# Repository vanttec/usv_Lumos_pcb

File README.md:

# vanttec-usv_Lumos_pcb 
PCB Led Strip/Expansión

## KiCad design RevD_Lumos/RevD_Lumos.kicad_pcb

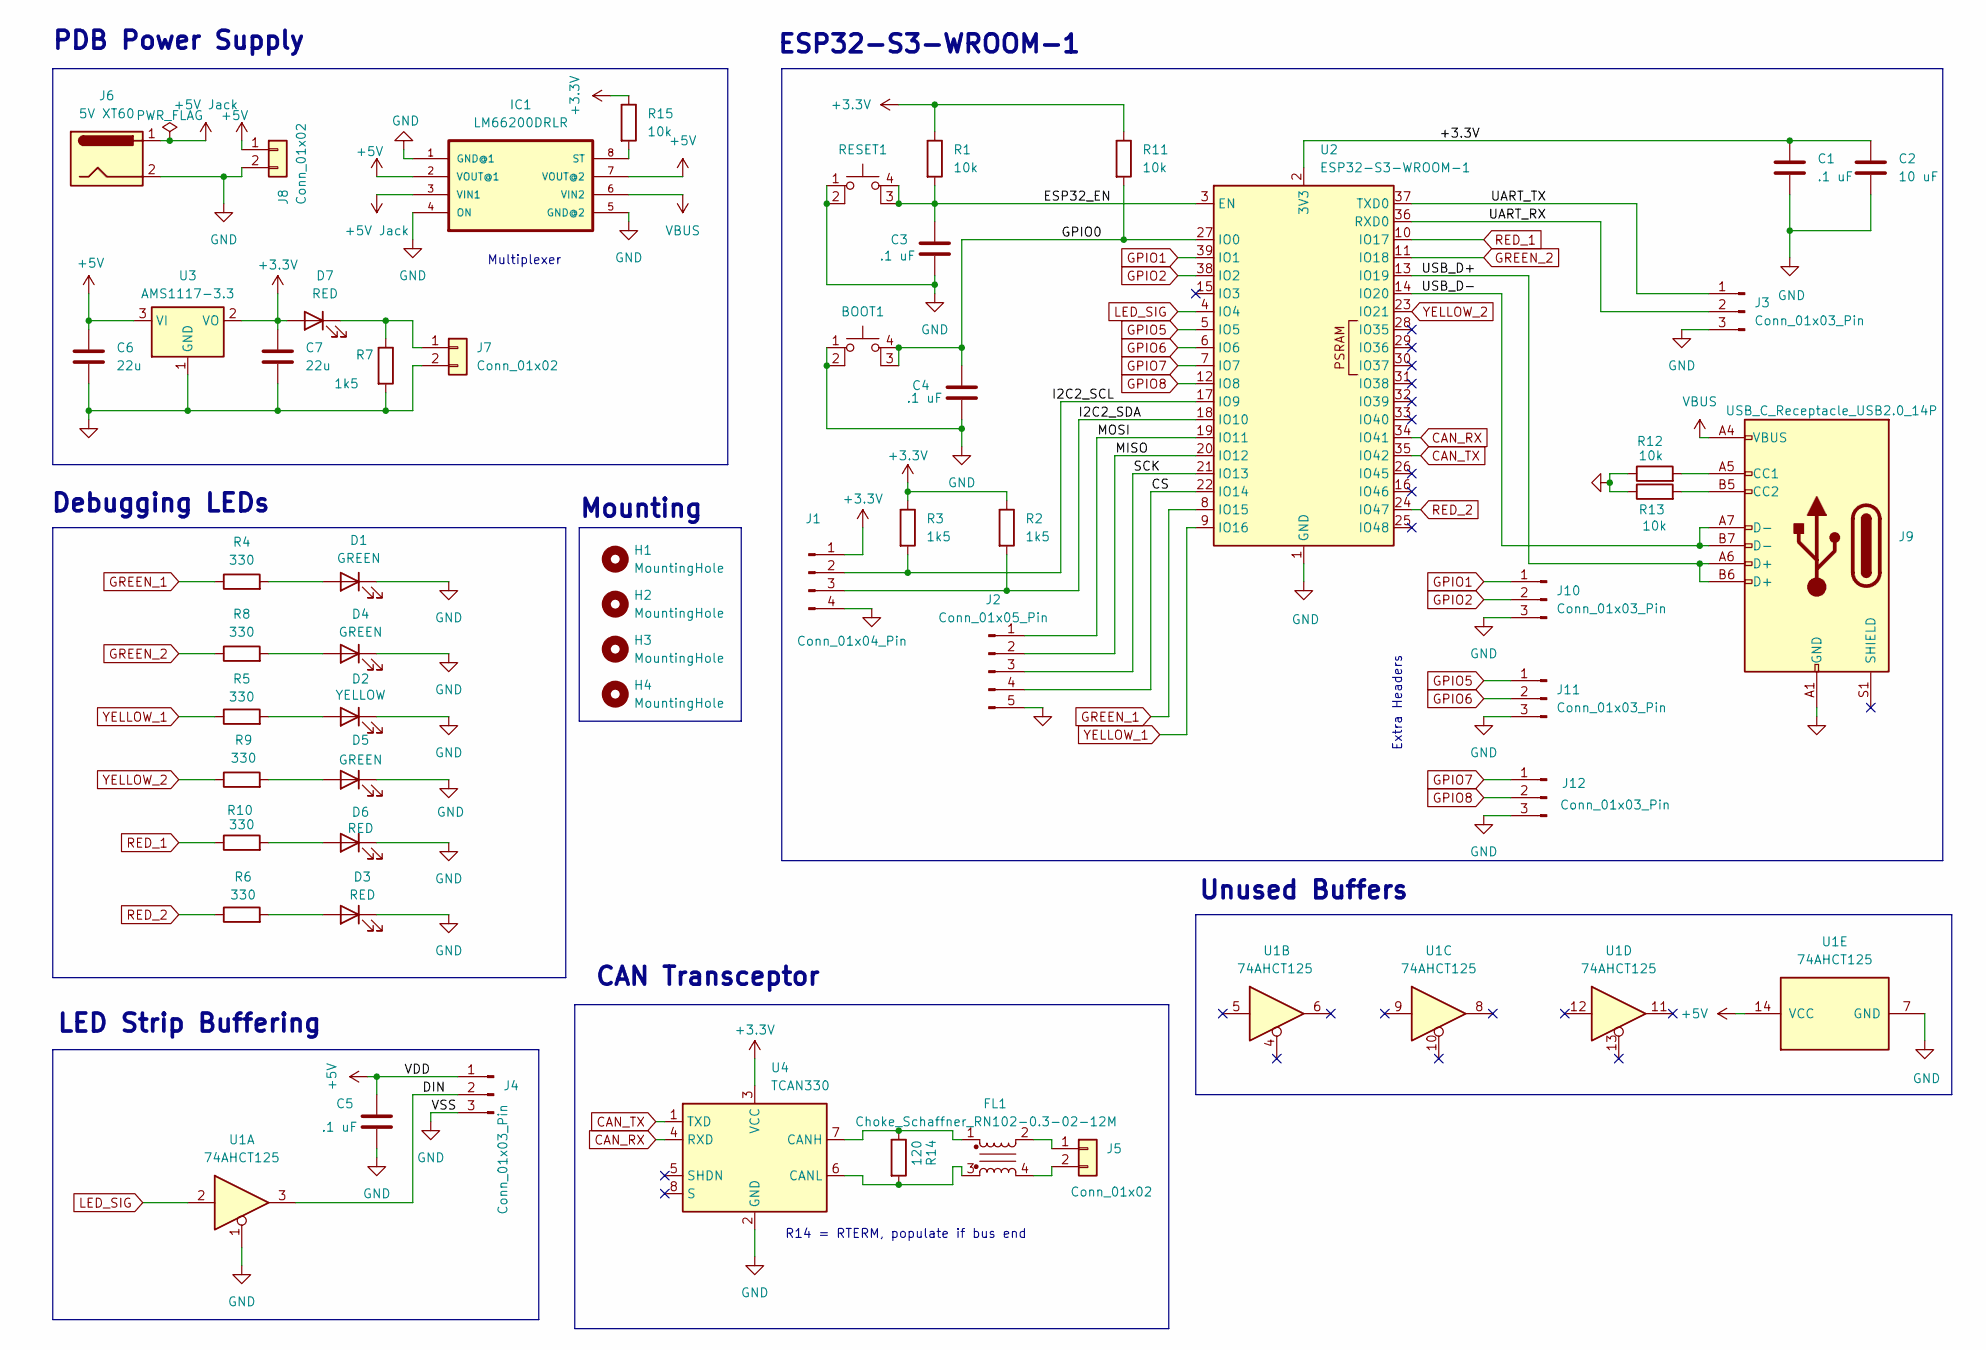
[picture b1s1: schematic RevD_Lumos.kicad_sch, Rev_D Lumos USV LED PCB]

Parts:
BOOT1: SW_MEC_5E; SW_MEC_5GSH9
C1, C3, C4, C5: .1 uF; C_0402_1005Metric
C2: 10 uF; C_0402_1005Metric
C6, C7: 22u; C_0805_2012Metric
D1, D4, D5: GREEN; LED_0603_1608Metric
D2: YELLOW; LED_0603_1608Metric
D3, D6, D7: RED; LED_0603_1608Metric
FL1: Choke_Schaffner_RN102-0.3-02-12M; Choke_Schaffner_RN102-04-14.0x14.0mm
H1, H2, H3, H4: MountingHole; MountingHole_2.2mm_M2
IC1: LM66200DRLR; SOT-5X3_DRL_TEX
J1: Conn_01x04_Pin; PinHeader_1x04_P2.54mm_Vertical
J2: Conn_01x05_Pin; PinHeader_1x05_P2.54mm_Vertical
J3, J4, J10, J11, J12: Conn_01x03_Pin; PinHeader_1x03_P2.54mm_Vertical
J5, J7, J8: Conn_01x02; PinHeader_1x02_P2.54mm_Vertical
J6: 5V XT60; BarrelJack_Wuerth_694102107102_1.0x3.9mm
J9: USB_C_Receptacle_USB2.0_14P; USB_C_Receptacle_Molex_105450-0101
R1, R11, R12, R13, R15: 10k; R_0402_1005Metric
R2, R3, R7: 1k5; R_0402_1005Metric
R4, R5, R6, R8, R9, R10: 330; R_0402_1005Metric
R14: 120; R_0402_1005Metric
RESET1: SW_MEC_5E; SW_MEC_5GSH9
U1: 74AHCT125; SOIC-14_3.9x8.7mm_P1.27mm
U2: ESP32-S3-WROOM-1
U3: AMS1117-3.3; SOT-223-3_TabPin2
U4: TCAN330; SOIC-8-1EP_3.9x4.9mm_P1.27mm_EP2.29x3mm

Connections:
+3.3V: C1.1, C2.1, C7.1, D7.2 (A), J1.1, R1.1, R2.1, R3.1, R11.1, R15.1, U2.2 (3V3), U3.2 (VO), U4.3 (VCC)
+5V: C5.1, C6.1, IC1.2 (VOUT@1), IC1.7 (VOUT@2), J4.1, J8.1, U1.14 (VCC), U3.3 (VI)
+5V Jack: IC1.3 (VIN1), J6.1
/CS: J2.4, U2.22 (IO14)
/DIN: J4.2, U1.3
/ESP32_EN: C3.1, R1.2, RESET1.3 (K), RESET1.4 (A), U2.3 (EN)
/GPIO0: BOOT1.3 (K), BOOT1.4 (A), C4.1, R11.2, U2.27 (IO0)
/I2C2_SCL: J1.2, R3.2, U2.17 (IO9)
/I2C2_SDA: J1.3, R2.2, U2.18 (IO10)
/MISO: J2.2, U2.20 (IO12)
/MOSI: J2.1, U2.19 (IO11)
/SCK: J2.3, U2.21 (IO13)
/UART_RX: J3.2, U2.36 (RXD0)
/UART_TX: J3.1, U2.37 (TXD0)
/USB_D+: J9.A6 (D+), J9.B6 (D+), U2.13 (IO19)
/USB_D-: J9.A7 (D-), J9.B7 (D-), U2.14 (IO20)
CAN_RX: U2.34 (IO41), U4.4 (RXD)
CAN_TX: U2.35 (IO42), U4.1 (TXD)
GND: BOOT1.1, BOOT1.2, C1.2, C2.2, C3.2, C4.2, C5.2, C6.2, C7.2, D1.1 (K), D2.1 (K), D3.1 (K), D4.1 (K), D5.1 (K), D6.1 (K), IC1.1 (GND@1), IC1.4 (ON), IC1.5 (GND@2), J1.4, J2.5, J3.3, J4.3, J6.2, J7.2, J8.2, J9.A1 (GND), J9.A12 (GND), J9.B1 (GND), J9.B12 (GND), J10.3, J11.3, J12.3, R7.2, R12.1, R13.1, RESET1.1, RESET1.2, U1.1, U1.7 (GND), U2.1 (GND), U2.40 (GND), U2.41 (GND), U3.1 (GND), U4.2 (GND)
GPIO1: J10.1, U2.39 (IO1)
GPIO2: J10.2, U2.38 (IO2)
GPIO5: J11.1, U2.5 (IO5)
GPIO6: J11.2, U2.6 (IO6)
GPIO7: J12.1, U2.7 (IO7)
GPIO8: J12.2, U2.12 (IO8)
GREEN_1: R4.1, U2.8 (IO15)
GREEN_2: R8.1, U2.11 (IO18)
LED_SIG: U1.2, U2.4 (IO4)
unnamed: D1.2 (A), R4.2
unnamed: D2.2 (A), R5.2
unnamed: D3.2 (A), R6.2
unnamed: D4.2 (A), R8.2
unnamed: D5.2 (A), R9.2
unnamed: D6.2 (A), R10.2
unnamed: D7.1 (K), J7.1, R7.1
unnamed: IC1.8 (ST), R15.2
unnamed: FL1.2, J5.1
unnamed: FL1.4, J5.2
unnamed: J9.A5 (CC1), R12.2
unnamed: J9.B5 (CC2), R13.2
unnamed: FL1.1, R14.1, U4.7 (CANH)
unnamed: FL1.3, R14.2, U4.6 (CANL)
RED_1: R10.1, U2.10 (IO17)
RED_2: R6.1, U2.24 (IO47)
VBUS: IC1.6 (VIN2), J9.A4 (VBUS), J9.A9 (VBUS), J9.B4 (VBUS), J9.B9 (VBUS)
YELLOW_1: R5.1, U2.9 (IO16)
YELLOW_2: R9.1, U2.23 (IO21)

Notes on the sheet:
Unused Buffers
Debugging LEDs
CAN Transceptor
Extra Headers
R14 = RTERM, populate if bus end
LED Strip Buffering
Multiplexer
Mounting
PDB Power Supply
ESP32-S3-WROOM-1

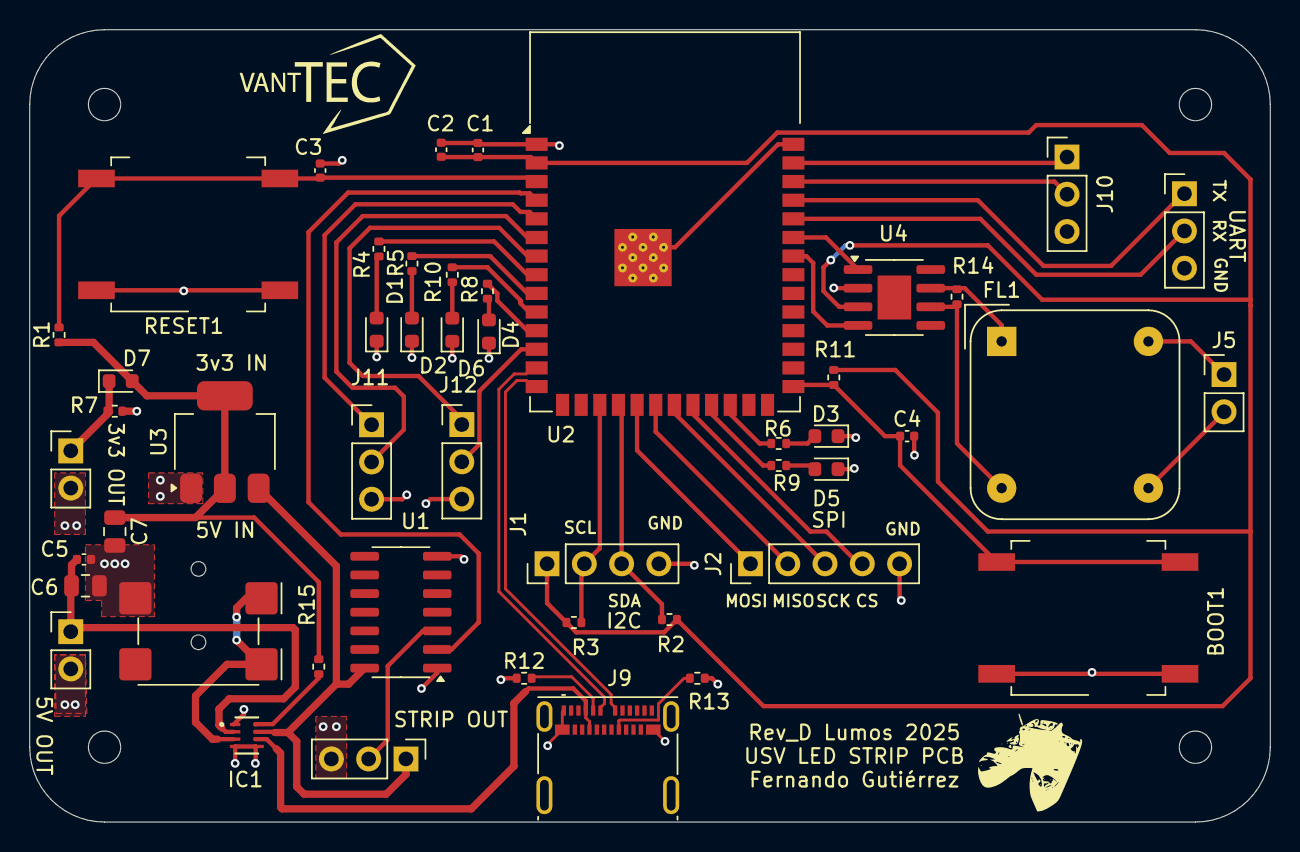
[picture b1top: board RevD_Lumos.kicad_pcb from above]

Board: 2 copper layers, 84.5 x 54.0 mm, 53 parts (0 on the bottom side), 47 nets.

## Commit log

2025-11-23 Initial Upload
2025-11-23 Setup
2025-11-30 Updated Multiplexer Footprint
